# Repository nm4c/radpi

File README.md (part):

<h1 align="center">
  <picture>
    <source media="(prefers-color-scheme: dark)" srcset="assets/logo/radpi-logo-dark.svg">
    
  </picture>
</h1>

RadPi puts a two-way radio on the web. A Raspberry Pi sits next to a radio, carries its own
transceiver on a HAT, or takes the place of an Icom radio's network mic, and anyone with a
browser can listen, talk and run the radio from anywhere, on a phone or a PC.

- **Remote operation:** receive audio and push-to-talk with low-latency WebRTC audio. Change
  channels or tune frequencies on a radio-style control head (a desk head on wide screens, a
  handheld on phones).
- **Three hardware options:**
  - The **RadPi Control HAT** drives an existing radio through its mic connector. It works with
    most land-mobile and UHF CB radios.
  - The **RadPi SA818 HAT** has a built-in 1 W UHF transceiver, with frequencies, CTCSS/DCS,
    a VFO and signal strength.
  - An **Icom IC-F6330D with its IP remote mic** needs no HAT at all. The Pi joins the network
    in the mic's place and speaks its protocol (reverse engineered from packet captures), so PTT,
    keys, audio and the radio's own screen all go over IP. The page draws the mic with its live
    LCD and LED, and channel presets jump across zones by typing the channel number.
- **On-air tools:** selcall (send and decode), audio clips played to air, text to speech in a
  choice of voices (Australian male and female included), recording of the channel, voice
  effects, and TX tone control.
- **AI agent (optional):**
  - It transcribes the channel and recognises who's talking.
  - It learns new voices and names, and keeps notes on people.
  - It can banter on air in a persona and voice you choose, including an Australian one you
    train yourself.
  - The models can run on the Pi, on an AI HAT+ 2, or in the cloud.
- **Several operators, safely:** personal accounts with control or listen-only roles, an audit
  log, and one transmitter at a time. Transmit time-outs drop PTT if a browser goes quiet.
- **Open source:**
  - Software: GPL-3.0.
  - Hardware: CERN-OHL-S. Both HATs are KiCad projects with JLC-ready parts.
  - Mock radio and audio backends let you try it all on a laptop.

There are three hardware modes, set with `radio.type` in `config.yaml`:

| `radio.type` | Hardware | Channels |
|---|---|---|
| `buttons` (default) | An external radio through the **[RadPi Control HAT](pihat/)** (or hand-wired optos, [docs/HARDWARE.md](docs/HARDWARE.md)) | The radio's own channels, stepped with UP/DOWN presses |
| `icom` | An **Icom IC-F6330D** with its PoE IP mic: the Pi takes the mic's network address, no HAT or wiring. See [Icom IP mic radio](#icom-ip-mic-radio-ic-f6330d) | Presets (zone, channel number, name): the Pi changes zone with LEFT/RIGHT, types the number, and confirms each change from the radio's screen. Channel changes made on the radio are followed |
| `sa818` | The **[RadPi SA818 HAT](sa818s-hat/)**: a 1 W UHF transceiver on the HAT, no external radio | A frequency/tone list in `config.yaml`, set over the module's serial port, plus direct frequency entry and a CTCSS drop-down (with optional tone squelch) per channel. Shows signal strength (RSSI) |

```
 Browser (phone / PC)                     Raspberry Pi                      Radio  
┌───────────────────┐   WebSocket    ┌──────────────────────┐  GPIO+opto  ┌──────────┐
│ PTT / CH▲▼ / list │◄──────────────►│ server (Python)      │────────────►│ PTT UP DN│
│ mic ─► Opus       │  JSON control  │  - PTT safety timers │  USB audio  │ MIC in   │
│ speaker ◄─ Opus   │◄══════════════►│  - channel tracking  │◄───────────►│ SPK out  │
│                   │ WebRTC (UDP)   │                      │             │          │
└───────────────────┘                └──────────────────────┘             └──────────┘
```

## Features

- Hold-to-talk button (mouse, touch or **Space** key). Mic audio streams to the radio.
- Low-latency audio over WebRTC (Opus over UDP), with automatic fallback to audio over the WebSocket.
  Settings shows the round trip and receive buffer.
- Receive audio with an RX level meter and a BUSY indicator.
- Channel ▲/▼ and jump-to-channel. The Pi presses UP/DOWN the right number of times.
- Channel names are set in config.
- Selcall: send 1-20 digit sequential tone calls from the radio face, and see calls heard on
  the channel. See [Selcall](#selcall).
- Audio clips: upload MP3s (or any audio the browser can play), pick one, and transmit it with
  the radio's Play key. See [Audio clips](#audio-clips).
- Say (off until you switch it on): type something, pick a voice, and the Pi speaks it on air.
  See [Say (text to speech)](#say-text-to-speech).
- Voice effects: Vader, Dalek, Demon, Robot, Giant, Female, Chipmunk and Ghost, switched on
  and off with the radio's P key. See [Voice effects](#voice-effects).
- Recording: the orange button records what the radio hears into 15-minute parts, which join the
  clip list. See [Recording](#recording).
- AI agent (off until you switch it on): transcribes the channel, recognises voices, learns new
  people, and can banter on air in a persona and voice of your choosing. See [AI agent](#ai-agent).
- A radio-style control head: a desk head on wide screens and a portrait handheld on phones.
  See [Control head](#control-head).
- With the RadPi SA818 HAT: frequencies, repeater offsets and CTCSS/DCS per channel, a VFO for any
  frequency in the band, and an RSSI bar on the display.
- With an Icom IC-F6330D: the radio's own mic drawn on the page, mirroring its screen, LED and
  keys, with every key (P1-P4, keypad, zone, squelch, volume, menu, power) pressed on the real
  radio. The real mic can stay in use alongside the page, or drive RadPi with any other radio.
  See [Icom IP mic radio](#icom-ip-mic-radio-ic-f6330d).
- Several operators can listen at once. Only one can transmit, and the others see who's on air
  and hear what they're sending, as they would on another radio (`audio.share_tx`).
- Personal accounts with **control** (everything) or **listen** (hear only) roles, an audit log of
  who did what, and login lockout. See [Accounts and security](#accounts-and-security).
- Safety features:
  - Server-side transmit time-out (`max_tx_seconds`).
  - PTT drops if the browser goes quiet (network loss, closed tab, phone locked).
  - PTT drops if the browser window loses focus.
  - No channel changes while transmitting.
  - GPIO pins stay low at boot.
- Mock GPIO and mock audio, so you can develop on a laptop without the radio.

## Try it on your laptop (no hardware)

```bash
cd radpi
python3 -m venv .venv && source .venv/bin/activate
pip install -r requirements.txt
cp config.example.yaml config.yaml
#  in config.yaml set: gpio.backend: mock, audio.backend: mock
python -m server.users -c config.yaml add me --role control    # asks for a password
python -m server -c config.yaml
```

Open <http://localhost:8080>. `localhost` counts as secure, so the mic works.
You'll hear a test tone burst every 10 s, and PTT/channel presses show in the server log.
Set `radio.type: sa818` to try the SA818S mode: the mock module answers commands and reports a wandering RSSI.
The mock audio also plays a received selcall (to `selcall.my_id`, or 12345) every 30 s.
Set `audio.backend: sounddevice` to use your laptop's own mic and speakers as a pretend radio.

## Control head

The top of the page is drawn as a radio. Wider screens get a desk control head and phones
(600 px and narrower) get a handheld. Both show the channel, name, frequency, TX with the
time-out countdown, BUSY, RSSI and signal bars.

| Control | Does |
|---|---|
| Channel knob (right on the desk head, the tall one on the handheld) | Picks a channel. The channel shows straight away in amber and is sent once you stop turning. |
| D-pad up / down | One channel up or down |
| Volume knob | Speaker volume, the same as the slider |
| Soft keys | Call (send the selcall number, or open the Selcall panel if none is entered), Play (transmit the picked audio clip; it shows Stop while a clip is on air), Chans (channel list, desk only), Tune (SA818) or Sync (button radios; desk only while clips are on), Setup (Settings) |
| Menu (handheld) | Settings |
| P (desk), P1 (handheld) | Switch the voice effect picked in the Voice effects panel on or off. The display shows FX while it's on. |
| Power (desk), held 1.5 s | Disconnect |
| Orange button (desk: top right; handheld: on top by the antenna) | Record: starts or stops recording received audio. While recording, any other control except the volume knob also stops it (and does nothing else). See [Recording](#recording). |

Knobs turn by dragging or with the mouse wheel. The handheld's top knobs roll with a swipe
across them. A focused knob also takes the arrow keys. PTT stays a separate button (or Space),
because neither head has one on its face.

The artwork is generated. Change `assets/control-head/build_template.py` (desk) or
`build_handheld.py` (handheld), then run them; they need `rsvg-convert` for the PNGs:

```bash
python3 assets/control-head/build_template.py && python3 assets/control-head/build_handheld.py
```

They write the app's SVGs and `radio_config.js` to `web/control-head/`, and PNG layers,
layout JSON and standalone test pages to `assets/control-head/output/`. The input handling,
`web/control-head/control_head.js`, is hand-written and shared by both templates.

## Selcall

Sequential tone calls of 1 to 20 digits, in the CCIR (100 ms tones), ZVEI-1 (70 ms) or EEA (40 ms)
standard (`selcall.standard`). Set `selcall.tone_ms` to run the standard's frequencies at another
tone length, such as CCIR at 50 ms. The decoder still hears calls with longer tones than that.
A digit that repeats the one before it is sent as the repeat tone.

- **Sending:** type the number in the Selcall panel, or tap a preset or an earlier call, then
  press the **Call** soft key. The Pi keys the radio, waits
  `tx_delay_ms` for the transmitter to come up, plays the tones into the mic line and unkeys.
  PTT is locked out while a call goes out, and a call can't start while anyone transmits.
- **Receiving:** the Pi watches the received audio for selcalls. Calls show on the head's bottom
  line, as a notice, and in the panel's list. A call to this station's `selcall.my_id` is
  highlighted and plays a short chime. Sequences shorter than `decode_min_digits` are ignored,
  so speech doesn't set it off. The decoder accepts tones up to about 2% off frequency.

The tones go out through the same audio path as voice, so `audio.tx_gain` and the sound card's
mixer apply (but not the TX tone control below, which would change their levels). Set `selcall.level` so the tones give normal deviation, about the same as speech.
Write selcall numbers in the config in quotes (`my_id: "01234"`), so leading zeros are kept.

## Audio clips

Recordings kept on the Pi and sent on air from the control head: a net opening, an ID, a test
message.

- **Adding:** in the Audio clips panel, press **Upload audio…** and choose one or more files.
  The browser converts each one itself (MP3, M4A, WAV, OGG: anything it can play), to mono at
  the wire rate, trims silence off the ends and uploads it. The Pi needs no audio codecs. Clips
  are limited to `clips.max_seconds` (60 s) and `clips.max_files` (50), and are shared by every
  operator.
- **Sending:** pick a clip, then press the **Play** soft key. The Pi keys the radio, waits
  `tx_delay_ms`, plays the clip and unkeys. While it plays, the key reads **Stop**, and any
  operator can press it to cut the clip off. PTT and selcalls are locked out meanwhile, and a clip
  can't start while anyone transmits. The transmit time-out still applies.
- **Level:** every clip is played with its peak at `clips.level`, so loud and quiet recordings
  go out alike. Like voice, it then goes through `audio.tx_gain` and the sound card's mixer.

The files are kept in `clips.dir` (`/opt/radpi/clips` on an install), as WAV files with
a `clips.json` list. `update.sh` leaves them alone. **Listen** next to a clip plays it in the
browser, where you can also save it. **Rename** gives a clip or recording a new name (up to
40 characters) for everyone; the file on the Pi keeps its ID, so nothing else changes.

## Recording

Press the orange button on the radio (or **Record** in the Audio clips panel) to record the
channel. Press it again to stop. While recording, pressing any other control except the
volume knob also stops it, and that press does nothing else.

- The display shows **REC**, and the panel shows the time so far and who started it.
- **Two modes**, picked with the tick box under the record bar before you start (the orange
  button uses the same setting; `record.mode` sets the default):
  - **Continuous:** everything, silence included.
  - **Only while the channel is active (VOX):** just the overs, back to back with a short gap
    (`vox_gap_ms`, 0.3 s) instead of the silence between them. "Active" means the busy line, or
    the RX level above `audio.busy_threshold_dbfs` without one, or us transmitting. Each over
    keeps `vox_preroll_ms` (0.5 s) from before it started, so the first syllable isn't lost, and
    recording runs on for `vox_hang_ms` (2 s) after it, so short pauses don't chop it up. The bar
    shows how much has been captured.
- **Both sides of the conversation.** While the radio is keyed its receiver is muted, so the
  recording takes what we send instead: voice (after any voice effect), selcalls and clips,
  copied from the sound card output in step with the received audio, at speech level whatever
  `audio.tx_gain` is. Turn this off with `record.include_tx: false`.
- Recordings are split into parts of `record.max_minutes` (15) of audio. When a part is full it
  joins the clip list as "Recording 08 Nov 14:05:00" and the next part starts with no gap.
  Stopping finishes the part in progress. In VOX mode a part is also finished after
  `vox_close_idle_minutes` (10) of quiet, so the overs so far appear in the list.
- It runs on the Pi, so it carries on with no one connected. It also carries on after a restart,
  and a part cut short by a power failure is recovered into the list.
- Storage: about 115 MB an hour. Once recordings pass `record.keep_mb` (2000 MB, about 17
  hours), the oldest are deleted. Uploaded clips are never deleted automatically. Recording
  stops, with a notice, if the disk gets down to `record.min_free_mb`.
- A recording can be played on air like any clip if it fits inside `ptt.max_tx_seconds`.
  Longer ones can't be picked, but you can still listen to and save them.

## Say (text to speech)

Type something in the **Say** panel, pick a voice and press **Say on air** (or Ctrl+Enter). The
Pi turns it into speech, keys the radio, waits `tts.tx_delay_ms` and speaks it, like a clip.
**Listen first** plays it in your own browser only, so you can check a voice or a tricky word
before it goes out. Off by default: set `tts.enabled: true` and list the voices in
`config.yaml` (see the `tts:` section of `config.example.yaml`).

- **Voices:** each one in `tts.voices` has a name for the list, a backend and that backend's
  voice. Mix them freely; the first is the default, and each browser remembers its last pick.

  | Backend | Australian voices | Notes |
  |---|---|---|
  | `azure` (Azure AI Speech) | `en-AU-NatashaNeural` (female), `en-AU-WilliamNeural` (male), and more | Natural sounding. Free tier. Needs `tts.azure.api_key` and `region` (e.g. `australiaeast`) |
  | `google` (Cloud Text-to-Speech) | `en-AU-Neural2-A`/`C` (female), `en-AU-Neural2-B`/`D` (male) | Needs `tts.google.api_key` |
  | `elevenlabs` | any Australian voice from its voice library | The most lifelike; small free tier. Needs `tts.elevenlabs.api_key` |
  | `piper` (offline, on the Pi) | none ready-made: [train your own](docs/voice/README.md) | British and American voices work out of the box. `sudo /opt/radpi/.venv/bin/pip install piper-tts`, then download a voice's `.onnx` and `.onnx.json` |

  The cloud voices need the internet and take about a second; Piper works with no connection.
- **Stopping:** while it speaks, any control operator can press **Stop**. PTT, clips and
  selcalls are locked out meanwhile, and Say can't start while anyone transmits. Text that takes
  longer than `ptt.max_tx_seconds` to say is refused, so split long messages up.
- **Level and words:** speech goes out with its peak at `tts.level`, through the TX tone
  control and `audio.tx_gain`. Add words it says wrong to `tts.pronounce`, spelled the way
  they should sound (`{"Wagga": "Wogga"}`).
- **Records:** each one is in the audit log (who, which voice, the text) and on the head's
  bottom line while it's on air. Listen-only accounts don't see the panel.
- **Keys:** the AI agent's voice (`bot.tts`) uses the same cloud keys if it doesn't have its own.

## Voice effects

Pick an effect in the **Voice effects** panel, then press **P** on the desk head (**P1** on the
handheld) to switch it on or off. The display shows **FX** while it's on, and the bottom line
briefly names the effect. Picking another effect while one is on switches straight to it, even
mid-transmission. Each operator has their own choice.

Every effect rebuilds the voice from scratch rather than just shifting it. The Pi splits your
speech into *what* is said (the shape of the mouth and throat, which carries the words) and *how*
your voice sounds (pitch, roughness, timbre), throws the second part away, and plays the first
through a new synthetic voice. Your own voice doesn't get through; only your timing and
articulation remain. Each effect then sets the new voice's size, pitch and colour:

| Effect | New voice |
|---|---|
| Vader | Bigger tract, 78 Hz, a metallic "mask" echo, light saturation |
| Dalek | Slightly small, near-monotone 95 Hz, through a 30 Hz ring modulator (as on the original) |
| Demon | Huge tract, 58 Hz with an octave-down growl, breath, distortion, a dark room |
| Robot | Monotone 100 Hz with a metallic comb |
| Giant | Big tract, 62 Hz, heavy bass, a large room |
| Female | Shorter tract, 205 Hz following your intonation, breathy |
| Chipmunk | Small tract, 330 Hz |
| Ghost | Whisper only (no pitch), with a long reverb |

The Pi applies the effect to your live voice only. Clips and selcalls go out unchanged, and the TX
tone control below still applies after the effect. Each effect is matched to the dry voice's
loudness and soft-limited, so deviation stays about the same. They add about 35 ms of delay.
Speak clearly: the new voice carries your articulation, and the strongest effects are harder to
understand on a weak signal. Each preset is a few lines in `server/voicefx.py` (warp = tract
size, f0 = pitch, keep = how much intonation survives) if you want to tune them.
Turn the feature off with `voice_fx: enabled: false`.

## AI agent

An optional agent that listens to the channel and can talk back. Turn it on with
`bot: enabled: true` in `config.yaml` (see the `bot:` section of `config.example.yaml`). An
**AI agent** panel then appears in the page. With `enabled: false` (the default) none of it loads
and the panel stays hidden.

Its Python packages (Whisper, the speaker model, Piper and PyTorch) come to well over a gigabyte,
so they're only installed if you ask:

- **New install:** `sudo ./deploy/install.sh --with-ai`.
- **Existing install:** `sudo ./deploy/update.sh --with-ai`. After that, plain `update.sh` keeps
  them up to date. Without the flag they're never downloaded.
- **Removing them:** `sudo ./deploy/update.sh --without-ai` rebuilds the venv without them.

For each over it:

1. Cuts it where the voice changes. On CB the next station often keys up the moment the last one
   lets go, so two or three people arrive as one recording. It checks the voice every ¾ second
   and splits at the changeover, and each part then goes through as an over of its own
   (`bot.split_overs`, sensitivity `bot.speaker.split`). A stretch where two stations are
   transmitting at once is labelled with the closest voice but never learned from.
2. Rates the audio. Through a repeater the signal strength is always good, so it listens for
   hiss under the words and crackle instead, and grades each over clean, rough or poor
   (`bot.quality`; hover over an over's details on the page for the numbers). A poor over is
   still transcribed and identified, but it isn't learned from, its level isn't taken as
   shouting, and the AI is told it was scratchy so it doesn't take misheard words literally.
3. Transcribes it: Whisper on the Pi's CPU (`faster_whisper`), or any OpenAI-compatible
   transcription server. Quiet stations are brought up to a normal level first. What Whisper
   makes up out of noise is dropped (stock phrases, loops, the vocabulary hint read back), and a
   repeater's tail can be cut off every over first (`bot.tail_ms`).
4. Works out who it was: a voiceprint (SpeechBrain ECAPA) compared with the people it knows.
   People you name are **known**. An unfamiliar voice is kept as **Caller N** and recognised next
   time, and becomes **acquainted** once it hears their name. Each person's voiceprint keeps a
   spread of their overs and matches on the closest few, so someone on two different radios is
   still one person. It only grows from overs that also match the ones certainly theirs (the
   first it heard, and any you name), so one wrong match can't snowball into a voiceprint that
   matches everybody. Callers that turn out to have the same voice are merged. When it isn't sure,
   it says so rather than guessing. Someone introducing themselves on air ("this is Bluey",
   "Bluey here", "Bluey to base") beats the voice match; just being called a name doesn't.
   To tune the thresholds (`bot.speaker`): `python -m server.bot people --similar`.
5. Decides whether to say something: an LLM gets the persona, what it knows about the speaker
   (their notes), the last few overs and the new one. It runs on Ollama, on hailo-ollama on the
   AI HAT+ 2 (Pi 5), or on any OpenAI-compatible server. It can also add to the speaker's notes
   and pick up their name.
6. Speaks: Piper offline (your own Australian voice: [docs/voice/README.md](docs/voice/README.md)),
   or Azure, Google or ElevenLabs Australian voices over the internet. With `bot.tones` on, it
   picks a tone for each reply: normal, raised or shout. It also hears when someone is shouting,
   from the over's level against the channel's usual. A raised or shouted reply is faster, higher
   and louder (the cloud voices), and is driven into the mic like someone yelling (every voice).

The panel shows the live transcript with who said what and how sure it is. Control operators can:

- Switch its mode:
  - **Listen**: transcribe and identify only.
  - **Approve**: each reply waits for **Send** or **Discard**.
  - **Auto**: replies go on air by themselves.
- Tick **Talk over people**. Normally it waits for a gap of `bot.reply_gap_ms` before keying up,
  and gives up if none comes; ticked, it transmits as soon as its reply is ready, whoever is
  talking (`bot.talk_over` is the start-up setting).
- Stop it mid-sentence.
- Name a voice from any over (**Name…**).
- Rename, merge or forget people.

Behaviour comes from the config and the persona prompt, not the code:

- The persona: `bot.persona`. Built in: `banter` (friendly, the default) and `cb` (foul-mouthed, gives as good as it gets), in `server/bot/prompts/`; or a path to your own file.
- When it speaks: `reply_policy` is `llm`, `always` or `addressed`.
- Rate limits: `max_replies_per_hour`, `min_reply_gap_s`. They're off by default.
- What it learns: `learn_anonymous`, `learn_notes`.

The code fixes only the radio mechanics:

- It waits for the channel to be quiet (`reply_gap_ms`) and never keys over anyone.
- Replies are capped at `max_reply_s`, and the server's transmit time-out still applies.
- Any operator can stop it.

Its transmissions go in the audit log as `kind: bot`.

Everything it learns is plain files in `bot.dir`. These can be read, edited and deleted directly:

- `people/people.json`: who it knows.
- `people/<id>.md`: notes on each person.
- `people/<id>.npy`: voiceprints.

The research log is `bot.dir/log/<date>.jsonl`. It records every over: transcript, speaker match
and score, and timings. It records every LLM decision, including the raw answer and silences, and
what happened to each reply (sent, dropped and why, discarded, stopped). With `keep_audio` it also
keeps each over's audio. `retention_days` prunes old logs and audio.

Try it without a radio, on recordings:

```bash
python -m server.bot -c config.yaml enrol --name Dave dave-1.wav dave-2.wav   # seed a known voice
python -m server.bot -c config.yaml replay overs/*.wav          # each file is one over
python -m server.bot -c config.yaml replay --split evening.wav  # cut a long recording into overs
python -m server.bot -c config.yaml people                      # who it knows
```

`replay` runs the full pipeline and writes the replies it would have sent as WAVs (`--out`). Use
`--dir` to keep test runs out of the live agent's memory.

Rough timings on a Pi 5:

| Step | Time |
|---|---|
| Whisper `base.en` | a few seconds per over |
| Speaker match | well under a second |
| A 1.5B model on the AI HAT+ 2 | a few seconds |
| Piper | faster than real time |

So expect roughly 4–10 s from un-key to reply. Mock backends (`backend: mock` for each) let you
try the panel on a laptop.

## TX tone control

Transmitted voice and clips pass through a bass and treble shelf on the Pi, because phone and
laptop mics often sound thin on FM. The defaults lift the bass by 6 dB below 400 Hz and ease the
treble by 3 dB above 2.5 kHz. Change them under `audio:` with `tx_bass_db`, `tx_bass_hz`,
`tx_treble_db` and `tx_treble_hz` (0 dB = flat; try a bass of up to 12 dB for a much fuller
sound). The radio passes only about 300-3000 Hz, so no setting adds bass below that. More bass
also raises the level, so recheck deviation after a big change. Selcall tones are not filtered.

## Display on the Pi

A [Pimoroni Display HAT Mini](https://shop.pimoroni.com/products/display-hat-mini) (2.0", 320×240)
on top of either RadPi HAT shows the channel, frequency and CTCSS, whether the channel is clear,
busy or on air (and who's transmitting), the signal, the last over the AI agent heard (who and
what they said), and who's logged in. Button X switches to a page with the Pi's address, host
name, temperature, uptime and the AI agent's state. A and B step the channel; Y turns the
backlight off (any button turns it back on).

Before fitting it:

- **Take the RGB LED off the display board** (or its three resistors). It's wired to GPIO 17, 27
  and 22, which are PTT, the SA818's power-down and its power level. RadPi never drives them for
  the display, but at boot, before the server sets them, the LED can pull the PTT line partway up.
- Fit your HAT with a **stacking header** (2×20, long pins), then the display on top.
- **Turn on SPI:** add `dtparam=spi=on` to `/boot/firmware/config.txt` and reboot.
- On the SA818 HAT, keep the antenna off the SMA: the display's edge is a few mm from it. Run coax
  to an antenna away from the case.

Then in `config.yaml`:

```yaml
display:
  enabled: true
  sleep_s: 300      # backlight off after 5 minutes of nothing (0 = always on)
  rotate: 180       # 0 if the picture is upside down in your case
```

Buttons can be changed under `display.buttons` (`channel_up`, `channel_down`, `page`,
`backlight` or `none` for each of `a`, `b`, `x`, `y`). The display's other pins (SPI CE1, GPIO 9
for data/command, 13 for the backlight, 5, 6, 16 and 24 for the buttons) are all free on both
RadPi HATs; the server refuses to start if a pin in `config.yaml` clashes with them.

For a quiet receiver the backlight is plain on/off (no dimming: PWM switching right over the
codec would be a whine on the audio), and the SPI clock is 20 MHz, whose harmonics (460, 480 MHz)
miss UHF CB. The screen is only redrawn when something on it changes. Listen on an empty channel
with the display on and off once: there should be no difference. To check the layout without the
hardware, set `gpio.backend: mock` and `display.mock_file: display.png`.

## Icom IP mic radio (IC-F6330D)

An Icom radio whose mic is a network device (the IC-F6330D's PoE IP mic) needs no HAT at all:
RadPi takes the mic's place on the network and speaks its protocol, which was worked out from
packet captures (`docs/ICOM-IP-MIC.md`). PTT, channel keys, the radio's screen and both directions
of audio all go over IP. The page draws the mic instead of the control head: its LCD and LED show
what the radio sends to the real mic, and its keys (P1-P4, the D-pad, the keypad, SIDE, VOL, EMERG
and power) are pressed on the radio, held for as long as you hold them. The side PTT bar is the
page's PTT. Selcall and clips get Send and Play buttons on the page, since the mic's keys belong
to the radio.

1. Give the Pi the mic's IP address (and unplug the mic), or program the radio with the Pi's.
   The radio connects to that address on TCP 52001; audio is RTP on UDP 50000 both ways.
2. In `config.yaml`: `radio.type: icom` and an `icom:` section (`radio_ip`, gains, presets).
   The page's channel buttons are `icom.presets`: each gives the zone (LEFT/RIGHT change zone,
   and each zone has its own channels), the channel's number in it and its name, exactly as the
   radio's screen shows them. Picking one presses RIGHT/LEFT until the zone's name shows, types
   the number on the keypad ("006") and waits for the channel's name. Changes made on the radio
   itself are followed: the matching preset lights up, or none if it's on another channel.
3. Set `icom.tx_gain` by ear on air: the radio expects mic level, and too much over-deviates.

**Several radios:** list them under `icom.radios` (each with its address, presets and zones). They
all stay connected and one is selected for everyone: buttons at the top of the page pick it, as does
P3 on the mic (`icom.switch_key`), which shows the radio's name before its screen. The others stay
silent but show BUSY on their button, and a real mic's LED flashes orange while one of them is
receiving. Switching waits for a transmission to finish.

**On a PC or server instead of a Pi:** with no HAT, nothing here needs a Pi. On Debian, Ubuntu,
Fedora or AlmaLinux (x86_64 or other), `sudo ./deploy/install-x86.sh` from the clone installs it,
starting from `config.icom.yaml` (the Icom settings only), on HTTPS port 443 with a self-signed
certificate until `deploy/cert-cloudflare.sh` gets a trusted one, and opens the radio's ports
(TCP 52001, UDP 50000) and 443 in firewalld or ufw. Run it again, or `update.sh`, to update.

There is no login or encryption in this protocol: keep it on a private network or VPN.
`python -m server.icom_cli` is a stand-alone mic for trying it from a terminal.

### The real mic as well, or as a control head for any radio

RadPi can also play the radio for a real IC-F6330D mic (`mic_head:` in `config.yaml`):

- **With `radio.type: icom`** RadPi sits between the radio and the mic, so both the mic and the
  web page work at once. The mic shows the radio's screen and its keys go to the radio as they
  are. Its PTT is RadPi's PTT for an operator called "Mic": the page shows "Mic" on air, and the
  audit log, the transmit time limit and one-at-a-time all apply. Program the radio's mic address
  as the Pi's.
- **With any other radio** the mic is a control head for RadPi: it shows the channel name, the
  LED is red while transmitting and green while the squelch is open, and the speaker plays what
  the radio hears. UP/DOWN change channel, the keypad types a channel number, VOL +/- set its
  speaker volume, and `mic_head.keys` gives the other keys a channel step, a selcall or a clip.

The mic only answers the radio address it was programmed with, and the radio sends it its
programming, so it's easiest to leave the mic alone and make the Pi look like the radio instead:
either give the Pi that address (`mic_head.local`, with the real radio off the network), or have
the router translate the Pi's traffic to the mic so it comes from that address (static source
NAT, ports kept as they are, both ways). RadPi connects from TCP port 52001, as the radio does;
the mic ignores connections from any other port.

Several mics can be connected at once (`mic_head.mics`): they all show the same screen and hear
the same audio, and PTT goes to whichever mic presses first, as with operators on the page; the
others show "NO TX". Each is named on the page and in the audit log ("Mic 1", "Mic 2", or a name
you give it). A mic programmed by a different radio expects that radio's address, so give each
one its own `local` address or NAT rule.

## Install on the Pi

1. Build the interface: see **[docs/HARDWARE.md](docs/HARDWARE.md)**. It has generic wiring plus IC-F621 notes.
   Or use the **[RadPi Control HAT](pihat/)**, a Pi HAT with the interface, sound card and power supply on one board.
2. Clone this repository on the Pi and run:
   ```bash
   sudo ./deploy/install.sh            # add --hat control or --hat sa818 with a RadPi HAT,
                                       #   and --with-ai to include the optional AI agent
   sudo nano /opt/radpi/config.yaml
   ```
   With a RadPi HAT, `--hat` (or `sudo ./deploy/setup-hat.sh control|sa818` later) sets the Pi up for
   it, Pi 4 or Pi 5: the codec as sound card "RadPi" and, for the SA818 HAT, the serial port. Reboot
   once, then `sudo ./deploy/setup-hat.sh --check` says whether everything is in place.
   Set `radio.type`, the channels (`channel.count` / `names` for an external radio,
   `channel.list` for the RadPi SA818 HAT; that board also needs the UART set up, see the `sa818:` section), and the sound card
   (`input_device` / `output_device`, for example `"USB Audio"`. List them with
   `/opt/radpi/.venv/bin/python -m sounddevice`).
3. Make your login: `sudo radpi-users add <your-callsign> --role control` (see
   [Accounts and security](#accounts-and-security)).
4. `sudo systemctl start radpi` and watch the log with `journalctl -u radpi -f`.

### Updating

Keep a git clone on the Pi (`git clone https://github.com/nm4c/radpi.git`) and run, from it:

```bash
sudo ./deploy/update.sh            # git pull, copy the code to /opt/radpi, restart
sudo ./deploy/update.sh --no-pull  # deploy the clone as it is, without pulling
sudo ./deploy/update.sh --with-ai  # also install the optional AI agent's packages (large download)
```

It copies only `server/`, `web/` and `requirements.txt` (and installs `radpi-users`), so
`config.yaml`, `state.json`, the account database `radio.db`, `tls/`, the audio clips and the
Python venv are left alone. It reinstalls Python packages only when `requirements.txt`
changed, reloads systemd only when the service file changed, and prints the log if the service
fails to come back up. New config options get their defaults until you add them to `config.yaml`
(see `config.example.yaml`).

The project used to be called Radio Remote. On an install from then (`/opt/radio-remote`),
the next `update.sh` moves everything to `/opt/radpi` (config, accounts, audit log, clips and
certificates), replaces the `radio-remote` service with `radpi` and `radio-users` with
`radpi-users`, and rebuilds the venv. Your clone keeps pulling from the old GitHub address, which
redirects; to tidy it up, run `git remote set-url origin https://github.com/nm4c/radpi.git`.

### Remote access over HTTPS (needed for the microphone)

Browsers only allow microphone access on `https://` or `localhost`. With Tailscale:

```bash
sudo tailscale serve --bg 8080
```

Then open `https://<pi-name>.<your-tailnet>.ts.net` on any device in your tailnet.
**WebRTC through a firewall:** the audio travels over UDP, on random ports unless
`webrtc.udp_ports` pins it to a range (e.g. `50100-50149`). On a Pi that has the public address
itself (4G), allow that range in its firewall (`sudo ufw allow 50100:50149/udp`). Behind a port
forward, forward the range (UDP) to the Pi along with the web port, and set
`webrtc.public_address` to the public address or DNS name. Without them browsers fall back to audio
over the WebSocket, which works but with more delay.

You can also set `server.tls_cert` / `tls_key` to your own certificate. For a free, browser-trusted one
from Let's Encrypt on a name in a Cloudflare-hosted domain, `sudo ./deploy/cert-cloudflare.sh radpi.example.com`
gets it with a DNS challenge (no open ports needed), renews it automatically, and prints the two lines to add.

### Using an iPhone

1. Install the Tailscale app and connect, then open the `https://…ts.net` address in Safari.
2. Tap **Share → Add to Home Screen** so it opens full-screen like an app.
3. Use headphones (wired or Bluetooth). iOS turns the loudspeaker down while a web page
   has the mic open.

Things to know:
- **Keep it on screen.** iOS pauses web audio and connections when the phone locks or you
  switch apps. The page keeps the screen awake while connected (iOS 16.4+), and drops PTT
  safely if it goes to the background.
- **After a call or Siri** the page shows "Audio paused. Tap here to resume". Any tap
  restarts audio, and if iOS released the mic, the next PTT press re-acquires it.
- **No hardware PTT.** A web page can't use the volume or headset buttons, so it's the
  on-screen button only.

## Accounts and security

Each operator logs in with their own username and password. Their display name (callsign) is
what other operators see and what the audit log records. Accounts live in `radio.db` (SQLite,
readable only by the `radio` user), managed with `radpi-users` on the Pi:

```bash
sudo radpi-users add vk3abc --role control --name "VK3ABC"   # asks for the password
sudo radpi-users add visitor --role listen
sudo radpi-users list                    # accounts, roles, last login
sudo radpi-users passwd vk3abc           # new password; ends that user's sessions
sudo radpi-users role visitor control    # promote / demote
sudo radpi-users disable visitor         # block logins, disconnect now
sudo radpi-users sessions                # devices kept logged in
sudo radpi-users logout vk3abc           # end all of a user's sessions
sudo radpi-users log --days 1            # the audit log
```

Changes apply within about 5 seconds, also to operators who are connected: a disabled account
is disconnected, and a demoted one loses PTT straight away.

| Role | Can |
|---|---|
| `control` | Everything: PTT, channels, tune/sync, selcalls, clips (upload, play, delete), recording, voice effects |
| `listen` | Hear the radio, see the channel, signal, who's transmitting, selcalls heard and the clip list, and listen to or save clips and recordings. The page hides the controls and never asks for the microphone; the server refuses those actions anyway. |

**Audit log.** Every login (and failed login), logout and disconnect; every transmission with its
duration, channel and kind (voice, voice effect, selcall, clip); channel changes, tune and sync;
selcalls; clip uploads, plays, stops and deletes; recording start and stop; voice effect changes;
refused actions from listen accounts; password and account changes. Kept for
`server.audit_days` (365). Read it with `sudo radpi-users log`.

**Passwords and sessions.**
- Passwords are stored as scrypt hashes, never in plain text, and must be at least 8 characters.
- "Keep me logged in" stores a random session token in the browser, never the password.
  Only a hash of the token is kept on the Pi. It lasts `server.session_days` (30) after its last
  use. Without the tick, the browser forgets it when the page closes.
- **Log out** in Settings ends the session on the Pi too. **Disconnect** keeps you logged in.
- Changing your password (Settings) logs out your other devices.

**Protection.**
- Five failed logins lock that address, and that username, for 15 minutes. A wrong username and
  a wrong password give the same answer and take the same time, so accounts can't be guessed.
- Strict security headers: only this server's own scripts and styles, and the page can't be
  framed by another site (so nobody can trick a click on PTT). The WebSocket refuses pages from
  other sites.
- Use HTTPS: `tailscale serve` (above) or your own certificate. Without it, passwords cross the
  network in the clear, and the server warns about that at start-up.

**Upgrading from the shared password.** If `server.password` is still set the first time the new
version starts, it becomes a `control` account called `operator`, so everyone can still get in.
Make personal accounts, then `sudo radpi-users delete operator` and remove `password` from
`config.yaml`.

## Channel tracking

(An Icom IP mic radio reads its channel from the radio's screen instead: see above.)
Mic-line button emulation can't read the channel back from the radio, so the Pi **tracks the
channel itself** and remembers it across restarts (`state.json`). If someone changes
channel on the radio's front panel, open **Settings → Set current channel** in the UI to
re-sync. No buttons are pressed.

## Protocol (for building other clients)

WebSocket at `/ws`. The first message must log in, with a password or an earlier session token:
`{"type":"auth","username":"vk3abc","password":"…","remember":true}` or
`{"type":"auth","session":"…"}`. The reply is
`{"type":"auth","ok":true,"name":"VK3ABC","username":"vk3abc","role":"control"|"listen","token":"…","session":"…"|null}`
(`session`: a new token after a password login) or `{"ok":false,"code":"login"|"session"|"locked","error":"…"}`.
Messages marked * need the `control` role; from a `listen` account they're refused with a notice.

| Direction | Message |
|---|---|
| → | \* `{"type":"ptt","on":true\|false}` |
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
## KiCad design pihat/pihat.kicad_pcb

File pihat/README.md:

# RadPi Control HAT

A Raspberry Pi HAT that replaces the hand-wired interface in [`../docs/HARDWARE.md`](../docs/HARDWARE.md).
It has everything on one board:

- **Opto-isolated control:** PTT, channel UP/DOWN and BUSY through a TCMT4100.
- **On-board sound card:** a TLV320AIC3104 I2S codec, with isolation transformers to the radio's
  mic input and speaker.
- **Power:** a 13.8 V input with protection, and a 5 V buck that also powers the Pi.
- **HAT ID EEPROM:** tells the Pi which sound-card overlay to load at boot.

| File | What it is |
|---|---|
| `pihat.kicad_pro` / `.kicad_sch` / `.kicad_pcb` | KiCad project |
| [`docs/schematic/radpi-control-hat.html`](docs/schematic/radpi-control-hat.html) | Reference schematic: 7 sheets, netlist, parts, pre-layout checks. Open it in a browser. |
| [`docs/BOM.md`](docs/BOM.md) | BoM notes and cost summary |
| [`docs/jlc-bom.csv`](docs/jlc-bom.csv) | JLCPCB assembly BoM |
| `docs/schematic/gen.py` | Regenerates the schematic page and the CSV from one parts list |
| [`docs/schematic.svg`](docs/schematic.svg) | The KiCad schematic, all sheets on one page (made by `tools/kicad/overview.py`) |

## Schematic

The whole circuit on one page, straight from the KiCad schematic (click to open it full size; part
and net names are searchable). Labels with the same name are connected. Regenerate it with
`python3 tools/kicad/overview.py` after changing the schematic.

## Software

**Pi set-up (Pi 4 or Pi 5):** from the git clone,

```
sudo ./deploy/setup-hat.sh control
sudo reboot
sudo ./deploy/setup-hat.sh --check
```

(or `sudo ./deploy/install.sh --hat control` on a new install). It installs the codec overlay
(`deploy/overlays/radpi-codec.dts`: the `tlv320aic3x` driver already in Raspberry Pi OS, codec at
I2C 0x18, reset on GPIO26, clocked from Y1's 12 MHz and driving the I2S clocks), and at the next boot
sets the codec's inputs and outputs (`deploy/radpi-mixer.sh control`: LINE1L in, HPLOUT and HPLCOM
differential into T1). The server finds the sound card ("RadPi") by itself. In `config.yaml`:
`radio.type: buttons`, the channels, and `gpio.busy_pin: 23` with `busy_pull_up: true` if the
radio's busy line is wired to BS+/BS-. Don't use the stock `dacberry400` overlay: its driver clocks
the codec's PLL from BCLK while telling it the clock is 12 MHz, so the sample rate would be wrong.

**Powering:** the HAT powers the Pi through header pins 2 and 4. Don't power the Pi from its USB-C
socket while the HAT is fitted and its 13.8 V input is off: the Pi's 5 V would then sit on the
buck's output with no input, which the LMR33640 datasheet says not to allow.

## Licence

The hardware design in this folder is licensed under the **CERN Open Hardware Licence v2, Strongly
Reciprocal (CERN-OHL-S-2.0)**. See [`LICENSE`](LICENSE). The generator scripts in `tools/` and
`docs/schematic/gen.py` are software and are GPL-3.0-or-later (see the repository root).

CERN-OHL-S asks that products made from the design say where the source can be found. Put this on
the board's silkscreen during layout, for example:

    RadPi Control HAT  CERN-OHL-S-2.0  github.com/nm4c/radpi

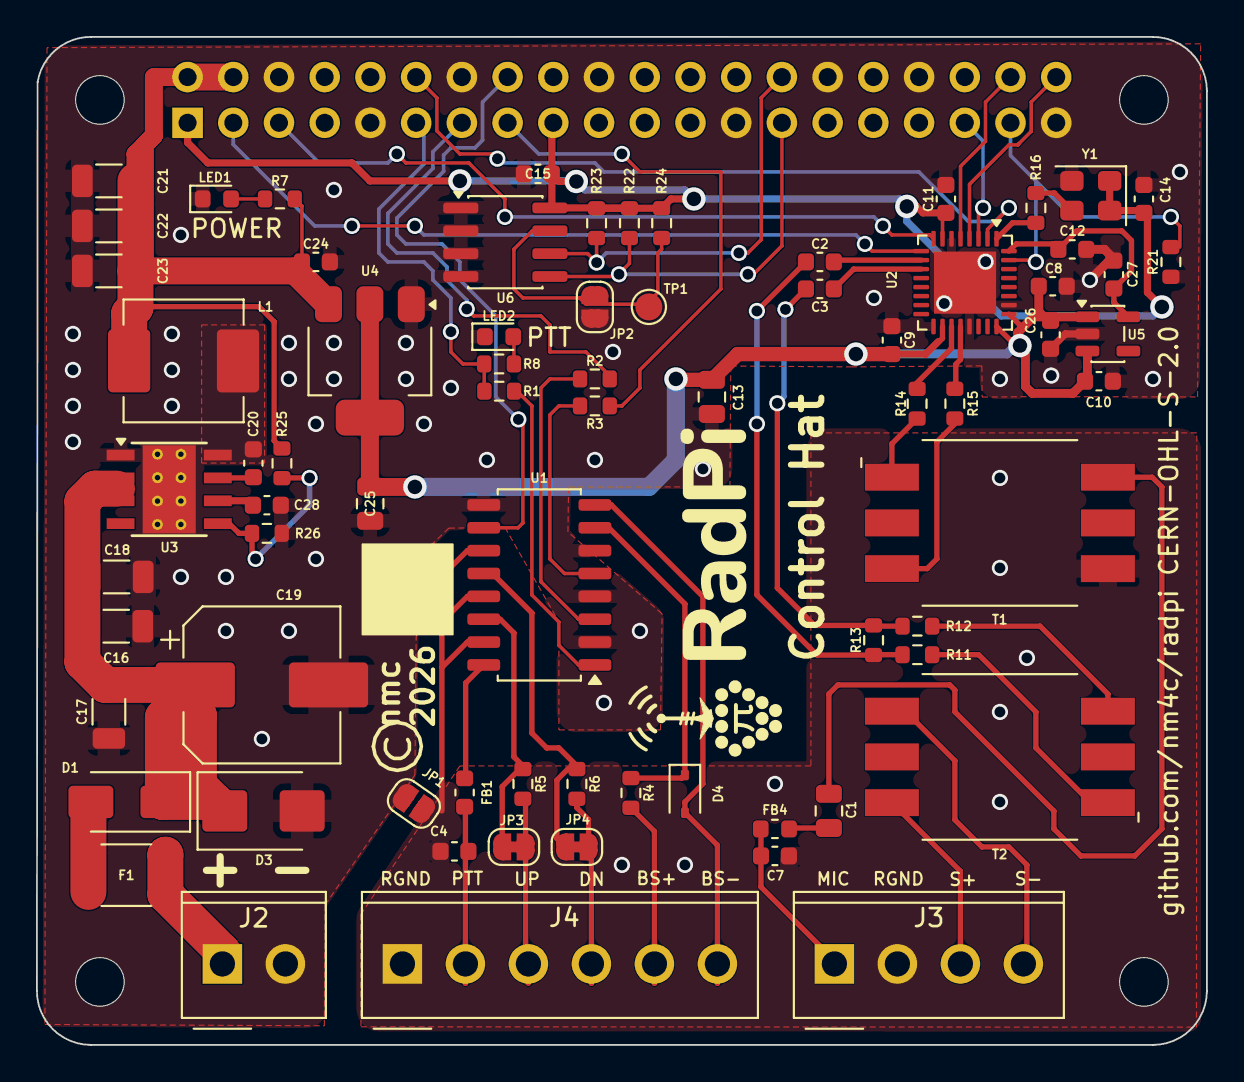
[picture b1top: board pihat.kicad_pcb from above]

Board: 2 copper layers, 65.0 x 56.0 mm, 77 parts (1 on the bottom side), 58 nets.

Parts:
C1: 1uF X7R; C_0805_2012Metric
C2, C3, C24, C26, C27, C28: 1uF; C_0603_1608Metric
C4, C7: 100pF; C_0603_1608Metric
C8, C9, C10, C11, C12, C14, C15, C20: 100nF; C_0603_1608Metric
C13, C25: 10uF; C_0805_2012Metric
C16, C17, C18: 2.2uF 50V; C_1206_3216Metric
C19: 100uF 50V; CP_Elec_8x10.5
C21, C22, C23: 22uF 25V; C_1206_3216Metric
D1: SS56; D_SMA
D3: SMBJ22A; D_SMB
D4: 1N4148WS; D_SOD-323
F1: 1.5A 33V; Fuse_1812_4532Metric
FB1, FB4: 600R@100MHz; L_0603_1608Metric
J1: GPIO; PinSocket_2x20_P2.54mm_Vertical
J2: 13.8 V in; Xinlaiya_XY2500V-F-3.5_1x02_P3.50mm_Vertical
J3: Audio; Xinlaiya_XY2500V-F-3.5_1x04_P3.50mm_Vertical
J4: Radio; Xinlaiya_XY2500V-F-3.5_1x06_P3.50mm_Vertical
JP1: RGND-GND; SolderJumper-2_P1.3mm_Open_RoundedPad1.0x1.5mm
JP2: WP write enable; SolderJumper-2_P1.3mm_Open_RoundedPad1.0x1.5mm
JP3, JP4: closed; SolderJumper-2_P1.3mm_Bridged_RoundedPad1.0x1.5mm
L1: 6.8uH 5A; L_Changjiang_FXL0630
LED1, LED2: red; LED_0603_1608Metric
MH1, MH2, MH3, MH4: MountingHole_2.7mm_M2.5
R1, R2, R3: 470; R_0603_1608Metric
R4: 2.2k; R_0603_1608Metric
R5, R6: ladder; R_0603_1608Metric
R7, R8, R24: 1k; R_0603_1608Metric
R11, R12, R13, R21: 10k; R_0603_1608Metric
R14, R15, R16: 33R; R_0603_1608Metric
R22, R23: 3.9k; R_0603_1608Metric
R25: 82k; R_0603_1608Metric
R26: 20k; R_0603_1608Metric
T1, T2: SM-LP-5001E; Bourns_SM-LP-5001
TP1: WP; TestPoint_Pad_D1.5mm
U1: TCMT4100; SOP-16_4.4x10.4mm_P1.27mm
U2: TLV320AIC3104IRHBR; QFN-32-1EP_5x5mm_P0.5mm_EP3.45x3.45mm
U3: LMR33640ADDAR; Texas_HSOP-8-1EP_3.9x4.9mm_P1.27mm_ThermalVias
U4: TLV76133DCYR; SOT-223-3_TabPin2
U5: TPS7A2018PDBVR; SOT-23-5
U6: AT24C32D-SSHM-T; SOIC-8_3.9x4.9mm_P1.27mm
Y1: 12MHz 3.3V; Oscillator_SMD_Abracon_ASE-4Pin_3.2x2.5mm

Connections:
+1V8: C12.1, C27.1, U2.32 (DVDD), U5.5 (OUT)
+3.3VA: C8.1, C9.1, C10.1, C13.1, C25.1, C26.1, U2.18 (DRVDD), U2.24 (DRVDD), U2.25 (AVDD), U4.2 (VO), U5.1 (IN), U5.3 (EN)
+3V3: C11.1, C14.1, C15.1, J1.1, J1.17, R22.1, R23.1, R24.1, U2.7 (IOVDD), U6.8 (VCC), Y1.1 (EN), Y1.4 (Vdd)
+5V: C21.1, C22.1, C23.1, C24.1, J1.2, J1.4, L1.2, R7.1, R25.1, U4.3 (VI)
/Codec/OSC_12M: R16.1, Y1.3 (OUT)
/Codec/U2_MCLK: R16.2, U2.1 (MCLK)
/EE_WP: JP2.1 (A), R24.2, TP1.1 (1_1), U6.7 (WP)
/ID_SCL: J1.28, R23.2, U6.6 (SCL)
/ID_SDA: J1.27, R22.2, U6.5 (SDA)
/Power/13V8_IN: F1.1, J2.1
/Power/FB: R25.2, R26.1, U3.5 (FB)
/Power/SW: C20.2, L1.1, U3.8 (SW)
/Power/VIN: C16.1, C17.1, C18.1, C19.1, D1.1 (K), D3.1 (K), U3.2 (VIN), U3.3 (EN)
/Power/VIN_F: D1.2 (A), F1.2
BUSY+: J4.5, R4.2
BUSY-: D4.2 (A), J4.6, U1.8
CODEC_RST: J1.37, R21.1, U2.31 (~RESET)
GND: C8.2, C9.2, C10.2, C11.2, C12.2, C13.2, C14.2, C15.2, C16.2, C17.2, C18.2, C19.2, C21.2, C22.2, C23.2, C24.2, C25.2, C26.2, C27.2, C28.2, D3.2 (A), J1.6, J1.9, J1.14, J1.20, J1.25, J1.30, J1.34, J1.39, J2.2, JP1.2 (B), JP2.2 (B), LED1.1 (K), LED2.1 (K), R21.2, R26.2, U1.2, U1.4, U1.6, U1.9, U2.6 (DVSS), U2.17 (AVSS1), U2.21 (DRVSS), U2.26 (AVSS2), U2.33 (EP), U3.1 (GND), U3.9 (GND), U4.1 (GND), U5.2 (GND), U6.1 (A0), U6.2 (A1), U6.3 (A2), U6.4 (GND), Y1.2 (GND)
GPIO17: J1.11, R1.1, R8.1
GPIO22: J1.15, R3.1
GPIO23: J1.16, U1.10
GPIO27: J1.13, R2.1
HP_N: R15.1, U2.20 (HPLCOM)
HP_P: R14.1, U2.19 (HPLOUT)
I2C_SCL: J1.5, U2.8 (SCL)
I2C_SDA: J1.3, U2.9 (SDA)
I2S_BCLK: J1.12, U2.2 (BCLK)
I2S_DIN: J1.40, U2.4 (DIN)
I2S_DOUT: J1.38, U2.5 (DOUT)
I2S_LRCLK: J1.35, U2.3 (WCLK)
unnamed: C1.1, T1.6
unnamed: C1.2, FB4.1
unnamed: C2.2, R11.1, R13.1
unnamed: C3.2, R12.1, R13.2
unnamed: D4.1 (K), R4.1, U1.7
unnamed: FB1.1, U1.16
unnamed: JP3.1 (A), R5.1, U1.14
unnamed: JP4.1 (A), R6.1, U1.12
unnamed: LED1.2 (A), R7.2
unnamed: LED2.2 (A), R8.2
unnamed: R1.2, U1.1
unnamed: R2.2, U1.3
unnamed: R3.2, U1.5
unnamed: R11.2, T2.1
unnamed: R12.2, T2.3
unnamed: R14.2, T1.1
unnamed: R15.2, T1.3
unnamed: C20.1, U3.7 (BOOT)
unnamed: C28.1, U3.6 (VCC)
RGND: C4.2, C7.2, J3.2, J4.1, JP1.1 (A), T1.4, U1.11, U1.13, U1.15
RX_N: C3.1, U2.11 (MIC1LM/LINE1LM)
RX_P: C2.1, U2.10 (MIC1LP/LINE1LP)
R_DN: J4.4, JP4.2 (B), R6.2
R_MIC: C7.1, FB4.2, J3.1
R_PTT: C4.1, FB1.2, J4.2
R_SPN: J3.4, T2.4
R_SPP: J3.3, T2.6
R_UP: J4.3, JP3.2 (B), R5.2

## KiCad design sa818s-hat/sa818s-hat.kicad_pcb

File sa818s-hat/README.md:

# RadPi SA818 HAT

A Raspberry Pi 4 HAT with a **built-in 1 W UHF FM transceiver**: no external radio. A NiceRF SA818S-U
module (400–480 MHz) is controlled by the Pi over a serial port, with audio through the same
TLV320AIC3104 I2S codec as the [RadPi Control HAT](../pihat/). It's meant for licensed amateur or
experimental use.

| Block | What's on the board |
|---|---|
| Transceiver | SA818S-U, frequency, CTCSS/DCS and squelch set over UART (9600 8N1, GPIO14/15) |
| Harmonic filter | 7th-order low-pass tuned for 400–480 MHz (−3 dB at about 550 MHz): 0.45–0.65 dB loss across the band, 0.62 dB at 477 MHz, return loss better than 22 dB, about −57 dB at the 2nd harmonic of 477 MHz (simulated with the parts' Q, ESR, self-resonance and tolerances). Murata LQW18AN 18 nH 2 % wirewound inductors (lowest-resistance 0603 version), Murata GJM high-Q C0G capacitors (5.6 pF ±0.1 pF, 13 pF ±2 %), all 0402 |
| Antenna | Vertical through-hole SMA (Amphenol 132134-11 footprint: any vertical THT SMA jack with legs on a 5.08 mm square), hand-soldered (not fitted by JLC), right at the filter output; the antenna screws on through the top of the case. Footprint for a 220 nH static-bleed inductor (L6, not fitted) |
| Control | PTT via MOSFET (boots in receive), high/low power via open-drain MOSFET, power-down on GPIO27, busy from the module's AudioON on GPIO23 |
| Audio | Codec headphone out → −30 dB → MIC_IN; AF_OUT → −6 dB → codec input. Direct, no transformers (shared ground). C0G coupling capacitors and thin-film resistors |
| Power | **From the Pi's 5 V only** (power the Pi from its USB-C socket; no input of its own). Module: TPS7A94 ultra-low-noise LDO at 4.2 V, then a ferrite + polymer-tantalum pi-filter. Codec: TPS7A2033 (3.3 V analog) and TPS7A2018 (1.8 V digital core), each from 5 V so the digital core's current pulses stay off the analog rail |
| ID EEPROM | AT24C32D, write-protected by default (R3 pull-up); ground test point TP1 while writing it |

## Schematic

The whole circuit on one page (click to open it full size; part and net names are searchable). Labels
with the same name are connected. Regenerate it with `python3 tools/overview.py` after changing the
schematic.

## GPIO use

| Pin | GPIO | Function |
|---|---|---|
| 8 / 10 | 14 / 15 | UART TX / RX to the module |
| 11 | 17 | PTT (high = transmit) |
| 13 | 27 | Module power: high = on, low = sleep (pulled low at boot) |
| 15 | 22 | Low power: high = 0.5 W, low = 1 W |
| 16 | 23 | Busy: low = signal present (`busy_pin: 23`, `busy_pull_up: true`) |
| 12, 35, 38, 40 / 3, 5 / 37 | 18–21 / 2, 3 / 26 | I2S, I2C and reset for the codec |

The UART set-up differs between the Pi 4 and Pi 5: see Software below.

## Files

| File | |
|---|---|
| `sa818s-hat.kicad_pro` / `.kicad_sch` / `.kicad_pcb` | KiCad project (from KiCad's built-in Raspberry Pi HAT template) |
| `sa818s-hat.kicad_sym`, `sa818s-hat.pretty/` | Project library: SA818S symbol and footprint, codec symbol |
| `docs/schematic.svg` | The full schematic on one page (made by `tools/overview.py`) |
| `tools/` | Generator for the sheets (`build.py`) and netlist check (`verify.py`). Uses the shared code in `../kicadgen/` and the power and codec sheets from `../pihat/tools/kicad/` |

## Before layout

- **Power budget** (official 5.1 V 3 A Pi supply): Pi 4 up to about 1.3 A, module 0.65–0.75 A on transmit at
  high power, codec and the rest under 50 mA: about 2.1 A. Power-hungry USB devices on the Pi can tip it over.
- **SA818S footprint:** pad positions agree between two independent footprints (one derived from LCSC/EasyEDA)
  and the datasheet drawing. Print it 1:1 and check a module against it before ordering.
- **RF layout:** 50 Ω grounded coplanar waveguide from the module's ANT pad through the filter to the SMA,
  short and straight, with ground vias beside every filter capacitor and a solid ground plane under the module.
  Leave room for a shield can over the module and filter.
- **Supplies:** place C38/C39/C40/C45 at the module's VBAT pad (C45, 100 pF, nearest the pin). U7 (TPS7A94):
  C31/C32 at IN and C33/C35 at OUT with their grounds together at U7's GND pin, no vias in between; SNS
  (pin 8) Kelvin to C33; thermal pad to a large ground area (about 0.6 W while transmitting).
- **12 MHz codec clock:** its 37th–39th harmonics are 444, 456 and 468 MHz (and 432 MHz). Keep Y1 and the
  MCLK trace (R16, 100 Ω to slow the edges) away from the module and the RF path, with ground pour around them.
  Avoid channels within a few kHz of those frequencies. If they're audible on receive, fit the shield can.
- **L6 (not fitted):** before fitting, measure U6 pin 12 for DC with the module receiving and transmitting into a
  dummy load. Fit it only if it reads 0 V.
- **Check harmonics** on a spectrum analyser after the first build, before connecting an antenna.
- **Frequency range:** the module covers 400–480 MHz (the SA818S-CE is the same module with CE-RED certification). NiceRF only promises power flat within 1 dB up to 470 MHz, so measure the output at your frequency.

## Software

Set `radio.type: sa818` in `config.yaml` (see `config.example.yaml`):

- `channel.list`: name, frequency, optional `tx_freq` for repeaters, `tone` (CTCSS Hz or DCS `D023N`),
  and per-channel bandwidth, squelch or low power.
- The web app shows the frequency and tones, an RSSI bar, and a box to tune any frequency in `sa818.band` (the VFO).
- At start-up the server wakes the module (PD), sets volume, audio filters and tail tone, then the channel.
  If the module stops answering, operators see the error, PTT is refused, and the server retries every 5 s.
- `gpio.busy_pin: 23` uses the module's AudioON as the BUSY indicator.
- RSSI is the module's raw reading, shown as dBm = reading × `sa818.rssi_db_per_step` + `sa818.rssi_offset_db`,
  kept between −127 and 0 dBm. The defaults (2.3 dB a step, −224) come from one module: about 45 with no signal
  (−121 dBm) and 65 for a −75 dBm signal. To calibrate yours, note the reading with no signal and with a known
  strong one, then step = (dBm difference) ÷ (reading difference) and offset = dBm − reading × step. Set the
  offset to `null` to show the raw reading.

**Pi set-up (Pi 4 or Pi 5):** from the git clone,

```
sudo ./deploy/setup-hat.sh sa818
sudo reboot
sudo ./deploy/setup-hat.sh --check
```

(or `sudo ./deploy/install.sh --hat sa818` on a new install). It installs the codec overlay (sound card
"RadPi"), sets the codec's inputs and outputs at the next boot, and frees the UART on GPIO14/15 for the
module: on a Pi 4, Bluetooth moved off it (`disable-bt`); on a Pi 5, `uart0` on; and on both, no serial
console or login prompt on it. `--check` says what's set up and how to fix anything that isn't. The server
then finds the port (`sa818.port: auto`), the sound card and the busy pin by itself.

Power the Pi from its own USB-C supply (official 5.1 V 3 A): the HAT has no power input.

## Licence

Hardware: CERN-OHL-S v2 (see [`LICENSE`](LICENSE)). The generator scripts are GPL-3.0-or-later (see the
repository root).

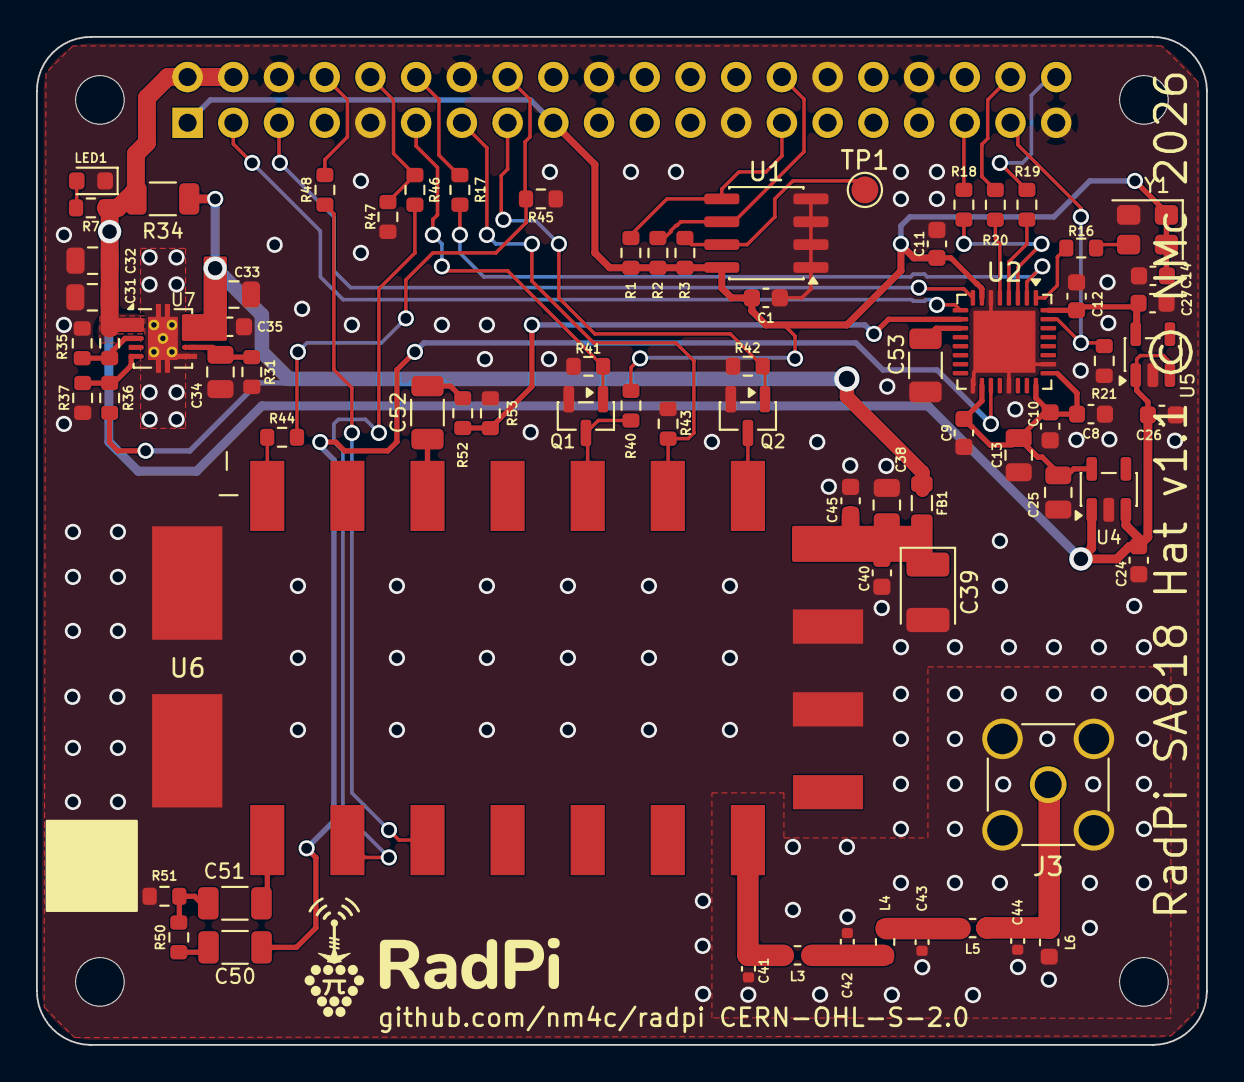
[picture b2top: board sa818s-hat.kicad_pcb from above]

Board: 2 copper layers, 65.0 x 56.0 mm, 80 parts (1 on the bottom side), 50 nets.

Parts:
C1, C8, C9, C10, C11, C12, C14, C40: 100nF; C_0603_1608Metric
C13: 10uF; C_0805_2012Metric
C24, C26, C27: 1uF X7R; C_0603_1608Metric
C25: 10uF X7R; C_0805_2012Metric
C31, C32, C33, C34, C38: 10uF X7R 16V; C_0805_2012Metric
C35: 1uF X7R 25V; C_0603_1608Metric
C39: 100uF 6.3V polymer; CP_EIA-3528-21_Kemet-B
C41, C44: 5.6pF; C_0402_1005Metric
C42, C43: 13pF; C_0402_1005Metric
C45: 100pF C0G; C_0603_1608Metric
C50, C51, C52, C53: 0.47uF C0G; C_1206_3216Metric
FB1: 220R 2A; L_0805_2012Metric
J1: GPIO; PinSocket_2x20_P2.54mm_Vertical
J3: SMA vertical THT; SMA_Amphenol_132134-11_Vertical
L3, L4, L5: 18nH 2%; L_0603_1608Metric
L6: 220nH DNP; L_0603_1608Metric
LED1: red; LED_0603_1608Metric
MH1, MH2, MH3, MH4: MountingHole_2.7mm_M2.5
Q1, Q2: 2N7002; SOT-23
R1, R2: 3.9k; R_0603_1608Metric
R3, R7: 1k; R_0603_1608Metric
R16: 100R; R_0603_1608Metric
R17, R18, R19, R20: 33R; R_0603_1608Metric
R21, R35, R37, R40, R44, R46, R48: 10k; R_0603_1608Metric
R31: 28.0k 0.1%; R_0603_1608Metric
R32, R45, R47: 22k; R_0603_1608Metric
R34: 0R DNP; R_1206_3216Metric
R36: 150k; R_0603_1608Metric
R41, R42, R43: 100k; R_0603_1608Metric
R50, R52, R53: 10k 0.1%; R_0603_1608Metric
R51: 330R 0.5%; R_0603_1608Metric
TP1: WP; TestPoint_Pad_D1.5mm
U1: AT24C32D-SSHM-T; SOIC-8_3.9x4.9mm_P1.27mm
U2: TLV320AIC3104IRHBR; QFN-32-1EP_5x5mm_P0.5mm_EP3.45x3.45mm
U4: TPS7A2033PDBVR; SOT-23-5
U5: TPS7A2018PDBVR; SOT-23-5
U6: SA818S-U; NiceRF_SA818S
U7: TPS7A9401DSCR; Texas_DSC0010J_ThermalVias
Y1: 12MHz 3.3V; Oscillator_SMD_Abracon_ASE-4Pin_3.2x2.5mm

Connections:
+1V8: C12.1, C27.1, U2.32 (DVDD), U5.5 (OUT)
+3.3VA: C8.1, C9.1, C10.1, C13.1, C25.1, U2.18 (DRVDD), U2.24 (DRVDD), U2.25 (AVDD), U4.5 (OUT)
+3V3: C1.1, C11.1, C14.1, J1.1, J1.17, R1.1, R2.1, R3.1, R40.1, U1.8 (VCC), U2.7 (IOVDD), Y1.1 (EN), Y1.4 (Vdd)
+4V2_RF: C38.1, C39.1, C40.1, C45.1, FB1.2, U6.8 (VBAT)
+5V: C24.1, C26.1, C31.1, C32.1, J1.2, J1.4, R7.1, R32.1, R34.1, U4.1 (IN), U4.3 (EN), U5.1 (IN), U5.3 (EN), U7.1 (IN), U7.2 (IN)
/Codec/OSC_12M: R16.1, Y1.3 (OUT)
/Codec/U2_BCLK: R17.2, U2.2 (BCLK)
/Codec/U2_DIN: R19.2, U2.4 (DIN)
/Codec/U2_DOUT: R20.2, U2.5 (DOUT)
/Codec/U2_MCLK: R16.2, U2.1 (MCLK)
/Codec/U2_WCLK: R18.2, U2.3 (WCLK)
/EE_WP: R3.2, TP1.1 (1_1), U1.7 (WP)
/ID_SCL: J1.28, R2.2, U1.6 (SCL)
/ID_SDA: J1.27, R1.2, U1.5 (SDA)
/RF power/EN_RF: R32.2, R35.1, U7.3 (EN_UV)
/RF power/NR_SS: C34.1, R31.1, U7.7 (NR/SS)
/RF power/PG_SET: R36.2, R37.1, U7.5 (FB_PG)
/RF power/VREG: C33.1, C35.1, FB1.1, R34.2, R36.1, U7.8 (SNS), U7.9 (OUT), U7.10 (OUT)
CODEC_RST: J1.37, R21.1, U2.31 (~RESET)
GND: C1.2, C8.2, C9.2, C10.2, C11.2, C12.2, C13.2, C14.2, C24.2, C25.2, C26.2, C27.2, C31.2, C32.2, C33.2, C34.2, C35.2, C38.2, C39.2, C40.2, C41.2, C42.2, C43.2, C44.2, C45.2, C53.2, J1.6, J1.9, J1.14, J1.20, J1.25, J1.30, J1.34, J1.39, J3.2, L6.2, LED1.1 (K), Q1.2 (S), Q2.2 (S), R21.2, R31.2, R35.2, R37.2, R41.2, R42.2, R43.2, R45.2, R47.2, R51.2, R53.2, U1.1 (A0), U1.2 (A1), U1.3 (A2), U1.4 (GND), U2.6 (DVSS), U2.17 (AVSS1), U2.21 (DRVSS), U2.26 (AVSS2), U2.33 (EP), U4.2 (GND), U5.2 (GND), U6.9 (GND), U6.10 (GND), U6.19 (GND), U6.20 (GND), U7.6 (GND), U7.11 (EP), Y1.2 (GND)
GPIO17: J1.11, Q1.1 (G), R41.1
GPIO22: J1.15, Q2.1 (G), R42.1
GPIO23: J1.16, R44.2, R45.1
GPIO27: J1.13, R43.1, U6.6 (PD)
HP_P: C50.1, U2.19 (HPLOUT)
I2C_SCL: J1.5, U2.8 (SCL)
I2C_SDA: J1.3, U2.9 (SDA)
I2S_BCLK: J1.12, R17.1
I2S_DIN: J1.40, R19.1
I2S_DOUT: J1.38, R20.1
I2S_LRCLK: J1.35, R18.1
unnamed: C42.1, L3.2, L4.1
unnamed: C43.1, L4.2, L5.1
unnamed: C50.2, R50.1
unnamed: C51.1, R50.2, R51.1
unnamed: C52.2, R52.1
unnamed: C44.1, J3.1, L5.2, L6.1
unnamed: LED1.2 (A), R7.2
unnamed: Q1.3 (D), R40.2, U6.5 (~PTT)
unnamed: Q2.3 (D), U6.7 (H/~L)
unnamed: C41.1, L3.1, U6.12 (ANT)
unnamed: R48.2, U6.16 (RXD)
unnamed: R46.1, U6.17 (TXD)
unnamed: R44.1, U6.1 (~AudioON)
RX_N: C53.1, U2.11 (MIC1LM/LINE1LM)
RX_P: R52.2, R53.1, U2.10 (MIC1LP/LINE1LP)
SA_AF: C52.1, U6.3 (AF_OUT)
SA_MIC: C51.2, U6.18 (MIC_IN)
UART_RXD: J1.10, R46.2, R47.1
UART_TXD: J1.8, R48.1

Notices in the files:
README.md:
This project is open source and share-alike: you can use, modify, build and sell it,
but anything you distribute that's based on it must be shared under the same terms.
Part | Licence | File
Software: `server/`, `web/`, `assets/control-head/`, `deploy/`, `kicadgen/`, `pihat/tools/`, `sa818s-hat/tools/`, `pihat/docs/schematic/*.py` | GNU GPL v3.0 or later | [`LICENSE`](LICENSE)
Hardware: the KiCad projects in `pihat/` and `sa818s-hat/` (schematics, PCB, symbols, footprints), `pihat/docs/` | CERN-OHL-S v2 | [`pihat/LICENSE`](pihat/LICENSE), [`sa818s-hat/LICENSE`](sa818
